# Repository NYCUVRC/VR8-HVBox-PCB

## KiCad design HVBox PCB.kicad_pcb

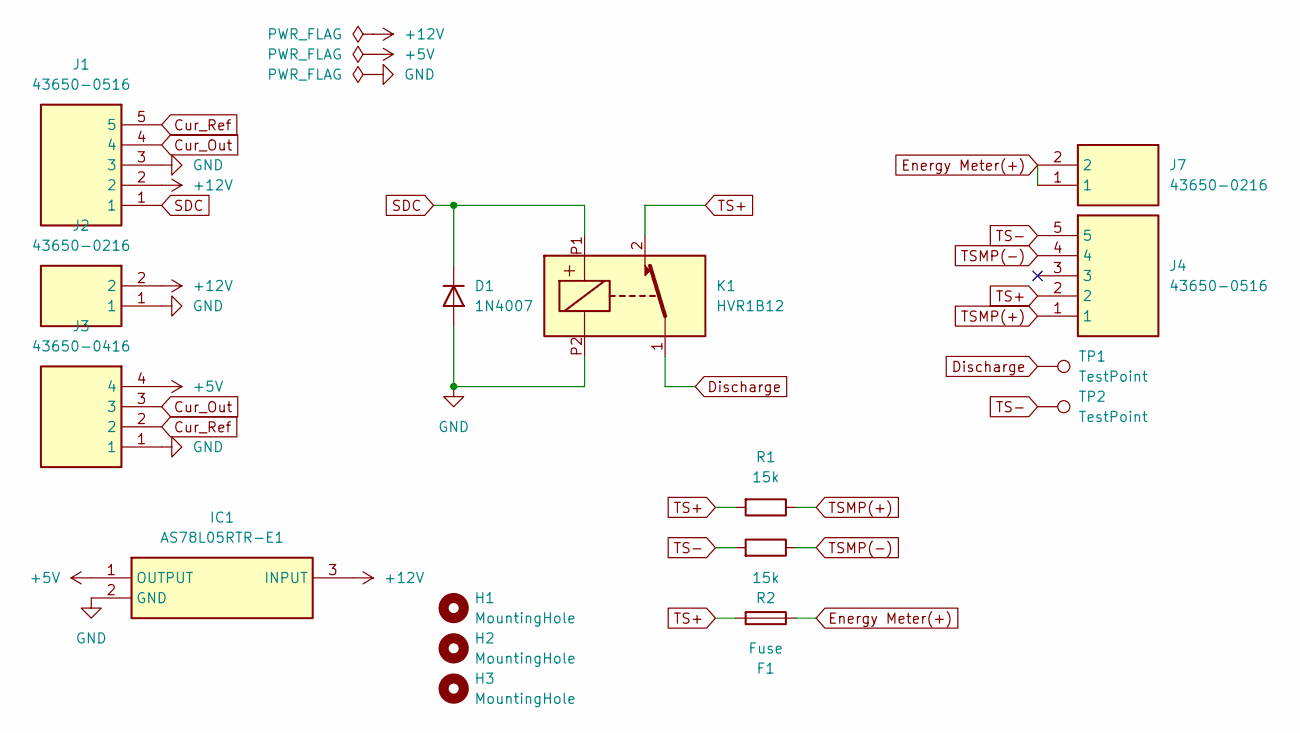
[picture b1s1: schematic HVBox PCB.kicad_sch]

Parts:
D1: 1N4007; D_DO-41_SOD81_P10.16mm_Horizontal
F1: Fuse; R_Axial_Power_L25.0mm_W6.4mm_P27.94mm
H1, H2, H3: MountingHole; MountingHole_4.3mm_M4
IC1: AS78L05RTR-E1; DIODES_SOT-89; Mouser Part Number 621-AS78L05RTR-E1
J1, J4: 43650-0516; 43650-05YY_151617; Mouser Part Number 538-43650-0516
J2, J7: 43650-0216; 43650-02YY_151617; Mouser Part Number 538-43650-0216
J3: 43650-0416; 43650-04YY_151617; Mouser Part Number 538-43650-0416
K1: HVR1B12
R1, R2: 15k; R_Axial_DIN0617_L17.0mm_D6.0mm_P20.32mm_Horizontal
TP1, TP2: TestPoint; TestPoint_THTPad_D2.5mm_Drill1.2mm

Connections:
+5V: IC1.1 (OUTPUT), J3.4
+12V: IC1.3 (INPUT), J1.2, J2.2
Cur_Out: J1.4, J3.3
Cur_Ref: J1.5, J3.2
Discharge: K1.1, TP1.1
Energy Meter(+): F1.1, J7.1, J7.2
GND: D1.2 (A), IC1.2 (GND), J1.3, J2.1, J3.1, K1.P2
SDC: D1.1 (K), J1.1, K1.P1
TS+: F1.2, J4.2, K1.2, R1.2
TS-: J4.5, R2.2, TP2.1
TSMP(+): J4.1, R1.1
TSMP(-): J4.4, R2.1

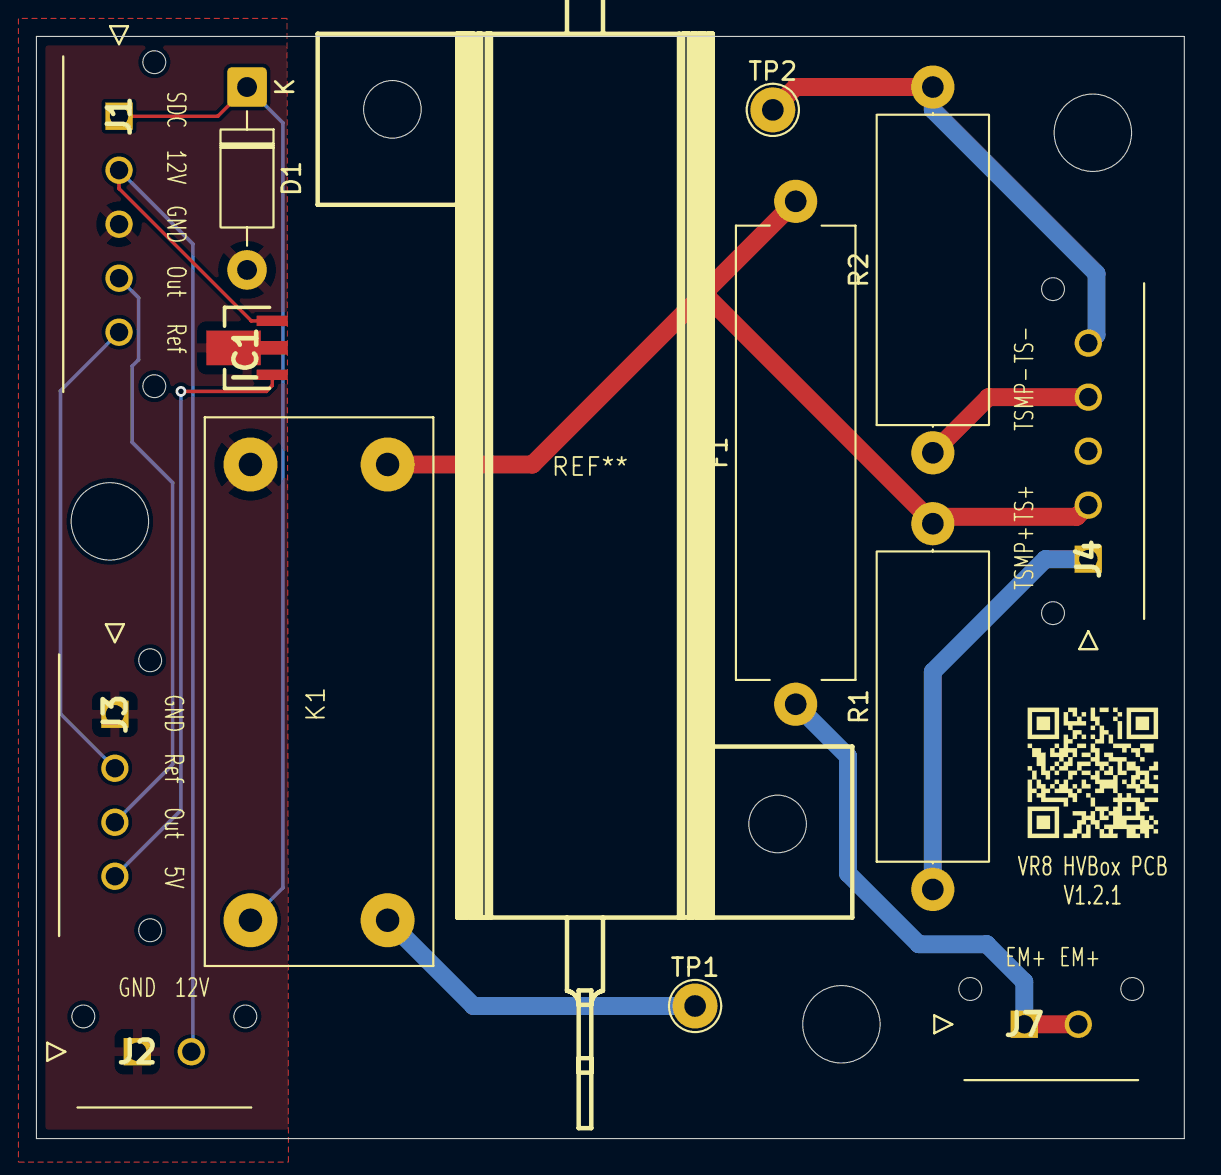
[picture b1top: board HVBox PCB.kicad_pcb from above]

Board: 2 copper layers, 63.8 x 61.2 mm, 17 parts (0 on the bottom side), 12 nets.

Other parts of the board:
QR*****: github

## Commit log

2025-12-21 remove files unnecessary
2025-12-21 fix: mismatch of schema and pcb
2025-12-30 better resister position
    Move resister from left to right to avoid interference of energy meter.
